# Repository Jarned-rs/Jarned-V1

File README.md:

# Jarned-V1

- A small hackpad used to automate the simpler things in life.
  
A practical mini keyboard for people who need to do things faster.

CASE:

 />

PCB:

Schematic:

How to use yourself!
Just download the files above, get your PCB and other parts, download the KMK firmware and enjoy!
All the keys are set to F13, F14 ect. so you can make your own shortcuts through Windows!

BOM:
- 1 Seeed XIAO RP2040#
- 5x MX-Style switches
- 1 EC11 Rotary Encoder
- 1 0.91" OLED
- 5x white blank DSA keycaps
- 4x M3x16mm screws
- 4x M3x5mx4mm heatset inserts

Features:
- 5 Keys that are set to F13,14,15 ect.
- A rotary encoder (volume knob) that can be used to increase, decrease and mute audio
- An OLED screen that can be set to anything within the screen size
- Custom PCB and 3D printable case
- KMK firmware on a Seeduino XIAO RP2040

How to run locally:
All that is needed is Curcuit Python 10.2.1 (or the one that corresponds with your chip), the latest KMK firmware and the libaries listed below from the Adafuit CircuitPython bundle and the Adafruit CircuitPython Fonts libraries:
- adafruit_displayio_ssd1306.mpy
- adafruit_display_text

How it works:
- The Jarned V1 features direct pin scanning for simplicity.
- It also has a XIAO monuted on the bottom of the case to leave room for the OLED
- KMK was used with an OLED to keep the code simple and accessibl
- F13-17 mapped keys to be able to add your own shortcuts through Windowsd

Credits:
KMK documentation - massive help in the coding process
The HackClub Stardance community - helped my really simple problems.

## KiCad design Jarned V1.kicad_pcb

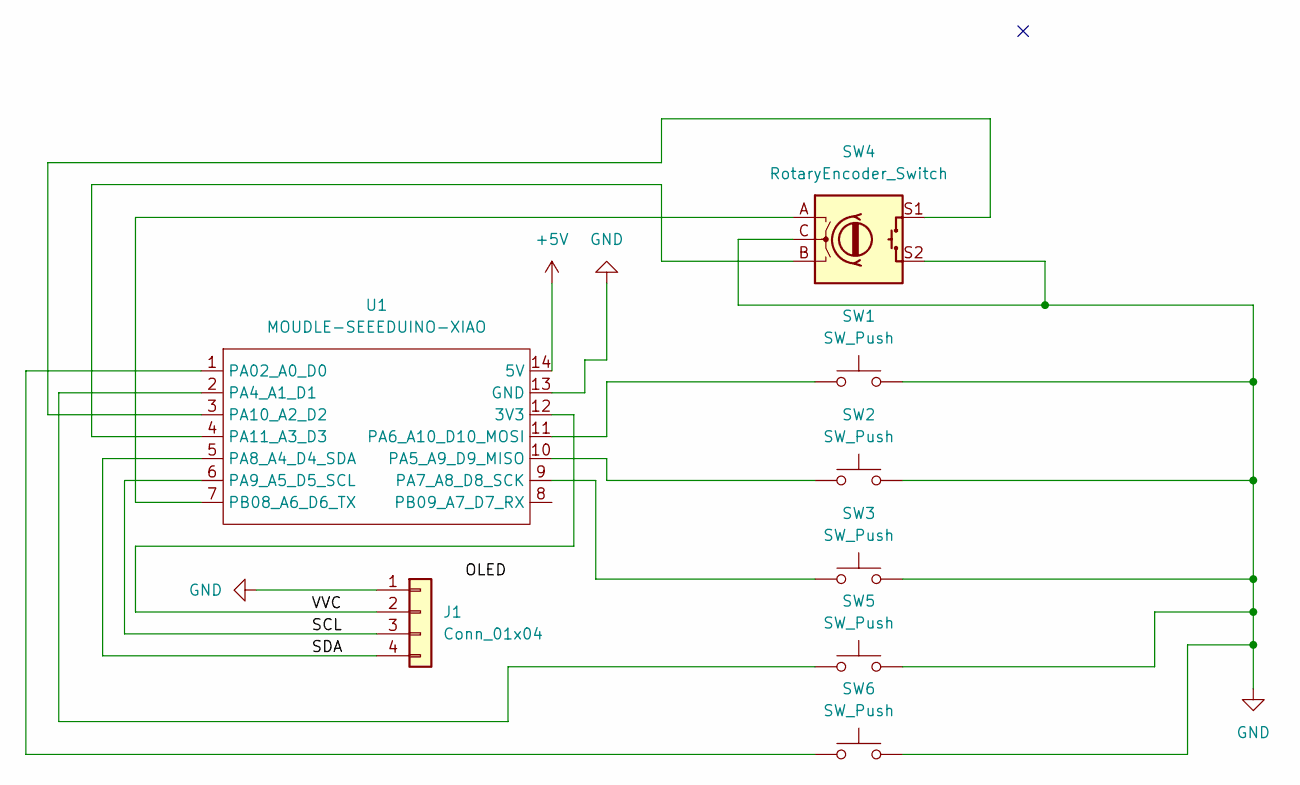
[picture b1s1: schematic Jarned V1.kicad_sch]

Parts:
J1: Conn_01x04; FanPinHeader_1x04_P2.54mm_Vertical
SW1, SW2, SW3, SW5, SW6: SW_Push; SW_Cherry_MX_1.00u_PCB
SW4: RotaryEncoder_Switch; RotaryEncoder_Alps_EC11E-Switch_Vertical_H20mm
U1: MOUDLE-SEEEDUINO-XIAO; XIAO-Generic-Hybrid-14P-2.54-21X17.8MM

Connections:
+5V: U1.14 (5V)
/SCL: J1.3, U1.6 (PA9_A5_D5_SCL)
/SDA: J1.4, U1.5 (PA8_A4_D4_SDA)
/VVC: J1.2, U1.12 (3V3)
GND: J1.1, SW1.2, SW2.2, SW3.2, SW4.C, SW4.S2, SW5.2, SW6.2, U1.13 (GND)
unnamed: SW6.1, U1.1 (PA02_A0_D0)
unnamed: SW5.1, U1.2 (PA4_A1_D1)
unnamed: SW2.1, U1.10 (PA5_A9_D9_MISO)
unnamed: SW1.1, U1.11 (PA6_A10_D10_MOSI)
unnamed: SW3.1, U1.9 (PA7_A8_D8_SCK)
unnamed: SW4.S1, U1.3 (PA10_A2_D2)
unnamed: SW4.B, U1.4 (PA11_A3_D3)
unnamed: SW4.A, U1.7 (PB08_A6_D6_TX)

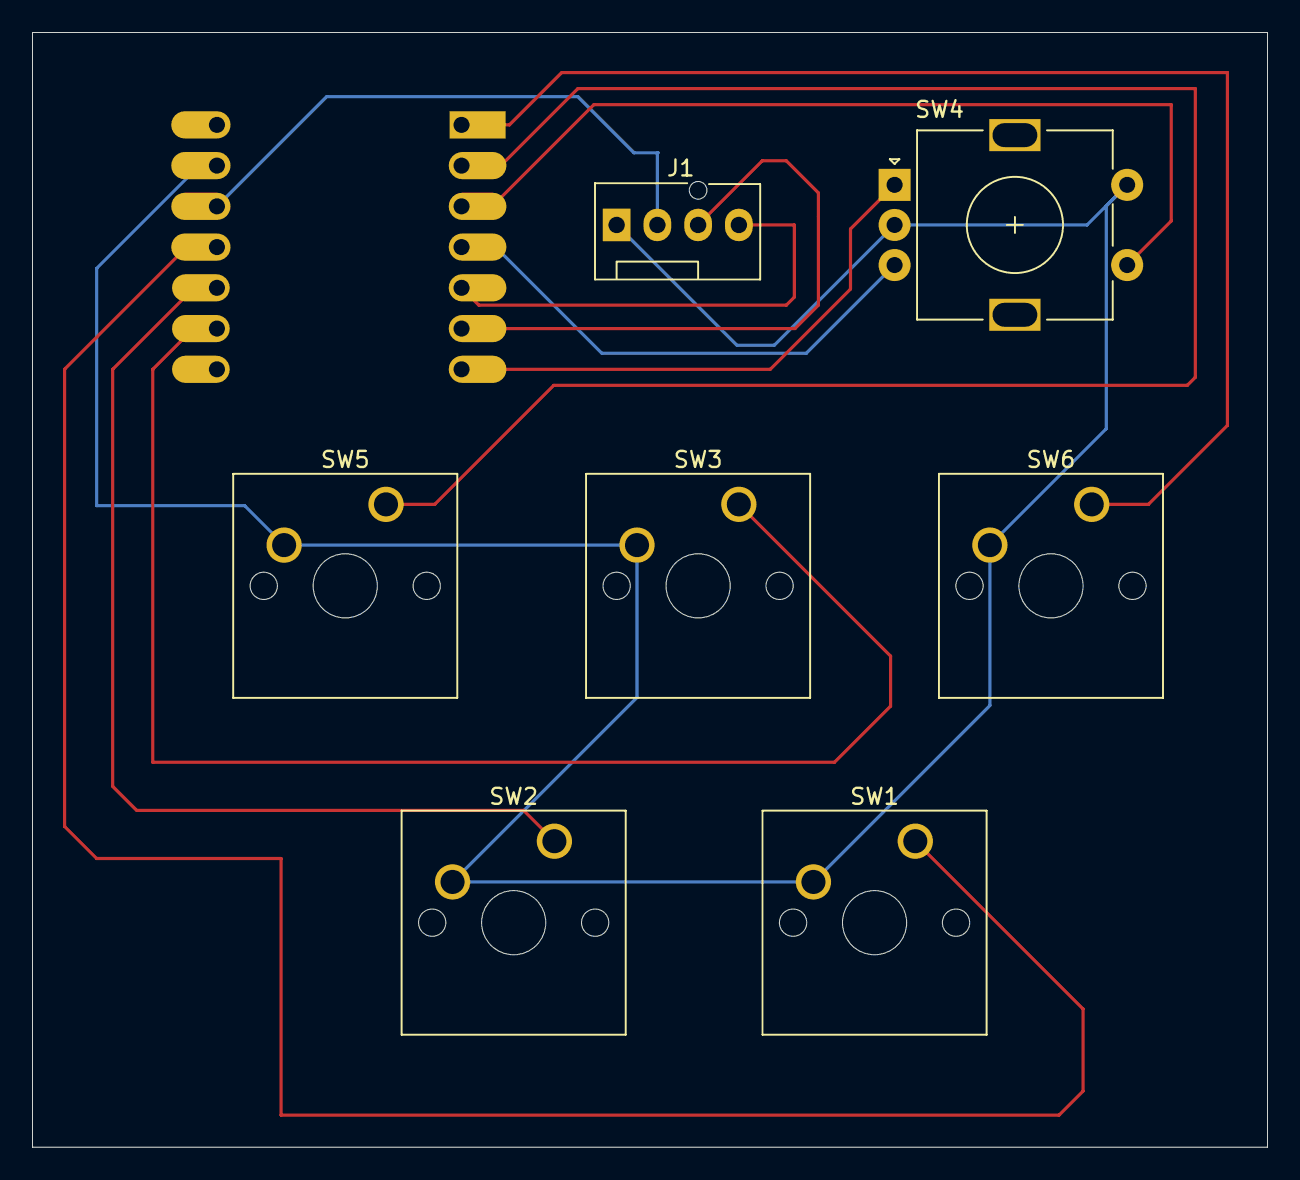
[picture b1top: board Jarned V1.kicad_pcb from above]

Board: 2 copper layers, 77.0 x 69.5 mm, 8 parts (1 on the bottom side), 12 nets.

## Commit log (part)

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2026-06-04 PCB complete
2026-06-04 Added a folder for the PCB items
2026-06-04 Create PCB folder
2026-06-04 Added PCB files into folder
2026-06-04 Create tester
2026-06-07 Updates KiCad skematics
2026-06-07 Added 3D models of the case
2026-06-08 Create test
2026-06-08 Actually write the README with some thought put into it
    Expanded README with detailed features, usage instructions, and credits.
2026-06-08 Rename demo.html to index.html
